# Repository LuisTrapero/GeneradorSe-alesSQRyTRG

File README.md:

# Generador Señales V1.0
Pequeño circuito diseñado en KiCad para generar señales cuadrada y triangular en fase. El circuito consta de cuatro partes:

1. **Un oscilador:** Empleamos el oscilador del circuito integrado CD4046 para generar una señal cuadrada de frecuencia variable. La frecuencia de las señales se puede ajustar mediante un potenciómetro o mediante una tensión externa al circuito.
2. **Un sumador:** para poder modificar el offset de la señal a nuestro gusto proponemos emplear un circuito sumador que utiliza como entrada la alimentación negativa de los amplificadores operacionales.
3. **Un integrador:** Tras dejar el offset de la señal cuadrada en 0V ya está preaparada para pasar por el integrador y convertirse en una señal triangular.
4. **Un divisor de tensión:** un simple instrumento para controlar la amplitud de la señal triangular.

Por comodidad en el montaje, la placa está diseñada para componentes through-hole.

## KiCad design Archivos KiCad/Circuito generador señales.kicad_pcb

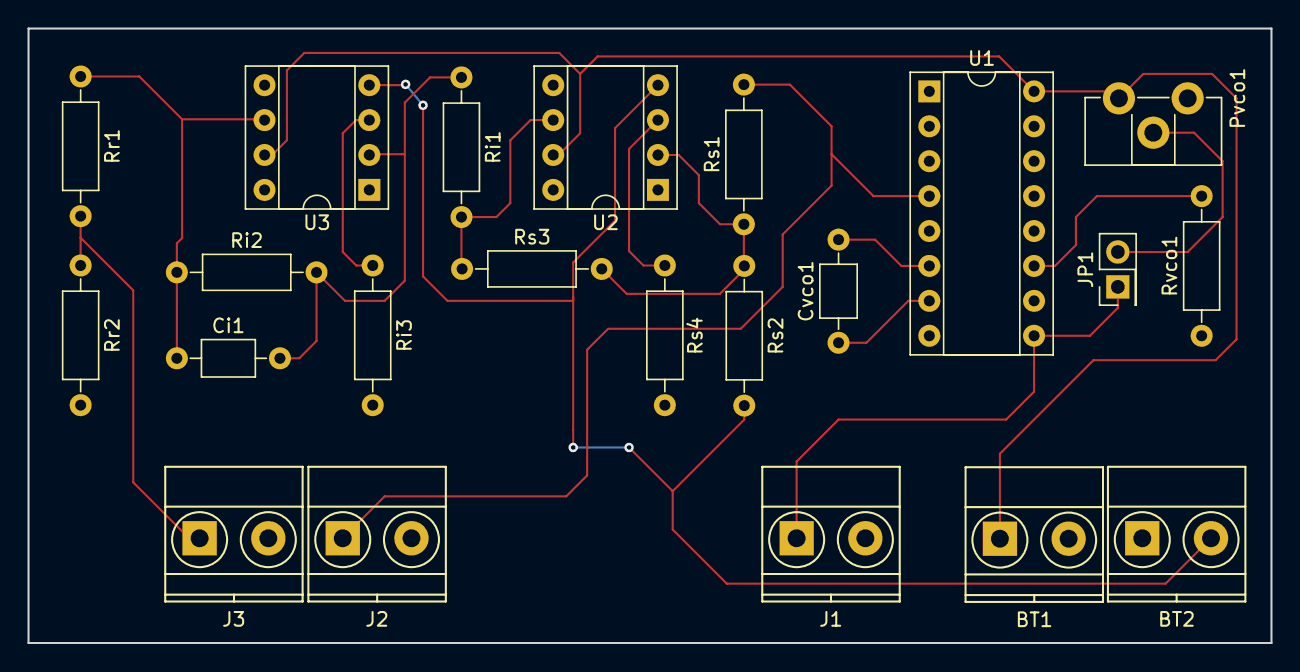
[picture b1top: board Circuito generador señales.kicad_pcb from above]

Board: 2 copper layers, 90.4 x 44.7 mm, 22 parts (0 on the bottom side), 16 nets.

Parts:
BT1: +5; TerminalBlock_Pheonix_MKDS1.5-2pol
BT2: -5; TerminalBlock_Pheonix_MKDS1.5-2pol
Ci1: 10n; C_Axial_L3.8mm_D2.6mm_P7.50mm_Horizontal
Cvco1: 100p; C_Axial_L3.8mm_D2.6mm_P7.50mm_Horizontal
J1: VCOin; TerminalBlock_Pheonix_MKDS1.5-2pol
J2: SQR; TerminalBlock_Pheonix_MKDS1.5-2pol
J3: TRNG; TerminalBlock_Pheonix_MKDS1.5-2pol
JP1: Jumper; Pin_Header_Straight_2x01_Pitch2.54mm
Pvco1: 10k; Potentiometer_Trimmer_ACP_CA9h2.5_Vertical_Px2.5mm_Py5.0mm
Ri1: 1.25k; R_Axial_DIN0207_L6.3mm_D2.5mm_P10.16mm_Horizontal
Ri2: 8k; R_Axial_DIN0207_L6.3mm_D2.5mm_P10.16mm_Horizontal
Ri3: 1k; R_Axial_DIN0207_L6.3mm_D2.5mm_P10.16mm_Horizontal
Rr1: 74.8k; R_Axial_DIN0207_L6.3mm_D2.5mm_P10.16mm_Horizontal
Rr2: 1k; R_Axial_DIN0207_L6.3mm_D2.5mm_P10.16mm_Horizontal
Rs1, Rs3: 10k; R_Axial_DIN0207_L6.3mm_D2.5mm_P10.16mm_Horizontal
Rs2: 20k; R_Axial_DIN0207_L6.3mm_D2.5mm_P10.16mm_Horizontal
Rs4: 1k; R_Axial_DIN0207_L6.3mm_D2.5mm_P10.16mm_Horizontal
Rvco1: 100k; R_Axial_DIN0207_L6.3mm_D2.5mm_P10.16mm_Horizontal
U1: 4046; DIP-16_W7.62mm_Socket
U2, U3: TL081; DIP-8_W7.62mm_Socket

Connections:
/-5V: BT2.2, Rs2.2, U2.4, U3.4
GND: BT1.2, BT2.1, J1.2, J2.2, J3.2, Pvco1.1, Ri3.2, Rr2.2, Rs4.2, Rvco1.1, U1.5, U1.8
unnamed: Ci1.1, Ri2.1, Rr1.1, U3.6
unnamed: Ci1.2, Ri1.1, Ri2.2, U3.2
unnamed: Cvco1.1, U1.7
unnamed: Cvco1.2, U1.6
unnamed: J1.1, JP1.1, U1.9
unnamed: J2.1, Rs1.2, U1.4
unnamed: J3.1, Rr1.2, Rr2.1
unnamed: JP1.2, Pvco1.2
unnamed: Ri1.2, Rs3.1, U2.6
unnamed: Ri3.1, U3.3
unnamed: Rs1.1, Rs2.1, Rs3.2, U2.2
unnamed: Rs4.1, U2.3
unnamed: Rvco1.2, U1.11
VDD: BT1.1, Pvco1.3, U1.16, U2.7, U3.7

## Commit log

2017-09-03 Testing Github Desktop
2017-09-03 Añadidos archivos KiCad
2017-09-03 Añadidas Datasheets de CIs
2017-09-10 Changed the structure of the repositories
